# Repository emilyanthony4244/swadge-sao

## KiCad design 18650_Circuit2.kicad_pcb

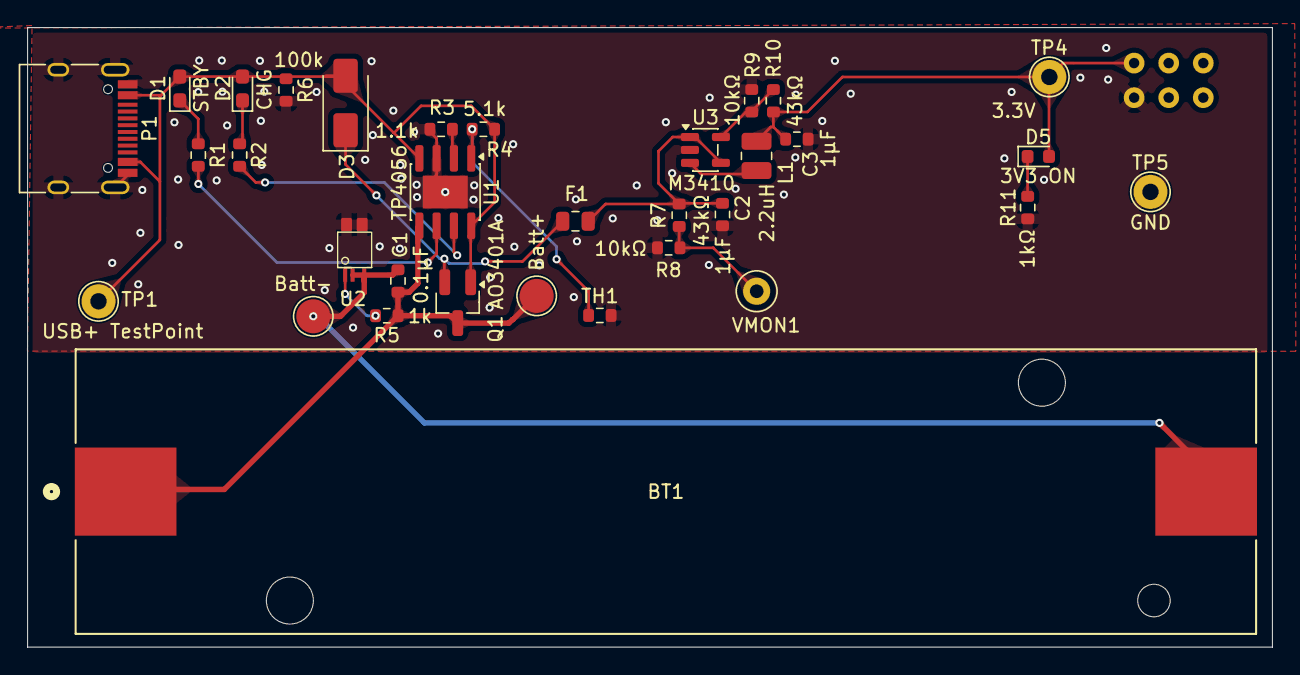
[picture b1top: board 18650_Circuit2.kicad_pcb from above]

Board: 2 copper layers, 91.4 x 45.5 mm, 34 parts (1 on the bottom side), 19 nets.

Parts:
BT1: Battery_Cell; BBC-S-G0 -A-18650-130
C1: 0.1μF; R_0603_1608Metric
C2, C3: 1μF; R_0603_1608Metric
D1: STBY; LED_0603_1608Metric_Pad1.05x0.95mm_HandSolder
D2: CHG; LED_0603_1608Metric_Pad1.05x0.95mm_HandSolder
D3: MBRS130LT3G-F; D_SMA
D5: 3V3 ON; LED_0603_1608Metric
F1: 500mA PTC; Fuse_0805_2012Metric
L1: 2.2uH; L_1008_2520Metric
P1: USB_C_Plug_USB2.0; USB_C_Receptacle_HRO_TYPE-C-31-M-12
Q1: AO3401A; SOT-23_Handsoldering
R1, R2, R5: 1k; R_0603_1608Metric
R3: 1.1k; R_0603_1608Metric
R4: 5.1k; R_0603_1608Metric
R6: 100k; R_0603_1608Metric
R7, R10: 43kΩ; R_0603_1608Metric
R8, R9: 10kΩ; R_0603_1608Metric
R11: 1kΩ; R_0603_1608Metric
TH1: Thermistor_NTC; R_0603_1608Metric
TP1: USB+ TestPoint; TestPoint_THTPad_D2.5mm_Drill1.2mm
TP2: Batt+; TestPoint_THTPad_D2.5mm_Drill1.2mm
TP3: Batt-; TestPoint_THTPad_D2.5mm_Drill1.2mm
TP4: 3.3V; TestPoint_THTPad_D2.5mm_Drill1.2mm
TP5: GND; TestPoint_THTPad_D2.5mm_Drill1.2mm
U1: TP4056; SOIC-8-1EP_3.9x4.9mm_P1.27mm_EP2.41x3.3mm_ThermalVias
U2: XB7608A
U3: M3410; SOT-23-5
U4: SAO
VMON1: TestPoint; TestPoint_Loop_D2.50mm_Drill1.0mm

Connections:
Batt +: BT1.1 (+), C1.1, Q1.3 (D), R5.1, TP2.1 (1_1), U1.5 (BAT)
Batt -: BT1.2 (-), C1.2, TP3.1 (1_1), U2.2 (GND), U2.3 (GND)
Charging: R2.2, U1.7 (~CHRG)
GND: C2.2, C3.2, P1.A1_B12 (GND), P1.A12_B1 (GND), P1.S1 (SHIELD), R3.2, R6.2, R8.2, R9.1, R11.1, TH1.2, TP5.1 (1_1), U1.3 (GND), U1.9 (EPAD), U2.4 (VM), U2.5 (VM), U3.2 (GND), U4.GND
unnamed: D1.1 (K), R1.1
unnamed: D2.1 (K), R2.1
unnamed: D3.1 (K), F1.2, Q1.2 (S)
unnamed: C3.1, D5.2 (A), L1.1, R10.2, TP4.1 (1_1), U4.3V3
unnamed: D5.1 (K), R11.2
unnamed: P1.A6 (DP1), P1.A7 (DN1), P1.B6 (DP2)
unnamed: R7.1, R8.1, VMON1.1 (1_1)
unnamed: R3.1, U1.2 (PROG)
unnamed: R4.2, TH1.1, U1.1 (TEMP)
unnamed: R5.2, U2.1 (VDD)
unnamed: R9.2, R10.1, U3.5 (FB)
unnamed: L1.2, U3.3 (LX)
SNODE: C2.1, F1.1, R7.2, U3.1 (EN), U3.4 (VIN)
Standby: R1.2, U1.6 (~STDBY)
VCC: D1.2 (A), D2.2 (A), D3.2 (A), P1.A4_B9 (VBUS), P1.A9_B4 (VBUS), Q1.1 (G), R4.1, R6.1, TP1.1 (1_1), U1.4 (V_{CC}), U1.8 (CE)
